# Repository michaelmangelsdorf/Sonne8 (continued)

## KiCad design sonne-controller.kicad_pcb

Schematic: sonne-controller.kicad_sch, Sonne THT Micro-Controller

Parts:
C1, C4, C6, C7, C16, C25, C26: C_Polarized_Small; CP_Radial_D6.3mm_P2.50mm
C2, C3, C5, C8, C9, C10, C11, C12, C13, C14, C15, C17, C19, C20, C21, C22, C23, C24: C_Small; C_Disc_D5.0mm_W2.5mm_P2.50mm
D1, D2: LED; LED_1206_3216Metric_Pad1.42x1.75mm_HandSolder
J1, J2, J4: Conn_01x08_Male; PinHeader_1x08_P2.54mm_Vertical
J3: Conn_01x20_Male; PinHeader_1x20_P2.54mm_Vertical
J5, J6: Conn_01x04_Male; PinHeader_1x04_P2.54mm_Vertical
J7: Conn_02x01; PinHeader_2x01_P2.54mm_Vertical
R1, R2, R3: R7.5k; R_Axial_DIN0207_L6.3mm_D2.5mm_P10.16mm_Horizontal
R4, R5: 500k; R_1206_3216Metric_Pad1.30x1.75mm_HandSolder
RN1, RN2: R_Network08; R_Array_SIP9
U1, U63: 4078; DIP-14_W7.62mm_Socket_LongPads
U2, U3, U5, U6, U7, U8, U19, U20, U25, U26, U29, U32, U49, U87: 74HC193; DIP-16_W7.62mm_Socket_LongPads
U4, U11, U45: 74HC74; DIP-14_W7.62mm_Socket_LongPads
U9, U34, U47, U50, U54, U94: 74AHC08; DIP-14_W7.62mm_Socket_LongPads
U12, U13, U16, U31, U52, U53, U56, U64, U65, U91, U92: 74AHC245; DIP-20_W7.62mm_Socket_LongPads
U14, U15, U21, U22, U23, U24, U69, U77, U78, U80, U81, U83, U89, U90, U96, U97: 74HC157; DIP-16_W7.62mm_Socket_LongPads
U17, U44, U98: 74AHC00; DIP-14_W7.62mm_Socket_LongPads
U18, U55, U60, U67, U68, U79, U82, U95, U99: 74AHC273; DIP-20_W7.62mm_Socket_LongPads
U27, U84: 74AHC02; DIP-14_W7.62mm_Socket_LongPads
U28, U38, U42, U46: 74HC32; DIP-14_W7.62mm_Socket_LongPads
U30, U33, U41, U43, U76, U88: 74AHC04; DIP-14_W7.62mm_Socket_LongPads
U35: KM62256CLP; DIP-28_W15.24mm_Socket_LongPads
U36: SST39SF040; DIP-32_W15.24mm_Socket_LongPads
U39: 4075; DIP-14_W7.62mm_Socket_LongPads
U40: 74HC163; DIP-16_W7.62mm_Socket_LongPads
U51, U72, U85, U86: 74HC238; DIP-16_W7.62mm_Socket_LongPads
U57: 27C080; DIP-32_W15.24mm_Socket_LongPads
U58, U59: 74HC283; DIP-16_W7.62mm_Socket_LongPads
U61: 74HC595; DIP-16_W7.62mm_Socket_LongPads
U62: 74HC165; DIP-16_W7.62mm_Socket_LongPads
U66, U70, U71, U74, U93: 74AHC138; DIP-16_W7.62mm_Socket_LongPads
U73, U75: 74AHC574; DIP-20_W7.62mm_Socket_LongPads
X1: CXO_DIP14; Oscillator_DIP-14

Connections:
+5V: C1.1, C2.1, C3.1, C4.1, C5.1, C6.1, C7.1, C8.1, C9.1, C10.1, C11.1, C12.1, C13.1, C14.1, C15.1, C16.1, C17.1, C19.1, C20.1, C21.1, C22.1, C23.1, C24.1, C25.1, C26.1, J2.5, J5.1, J6.1, J6.2, R1.1, R2.1, R3.1, R4.2, U1.14 (Vdd), U2.11 (~LOAD), U2.16 (VCC), U3.11 (~LOAD), U3.16 (VCC), U4.2 (D), U4.10 (~S), U4.12 (D), U4.13 (~R), U4.14 (VCC), U5.16 (VCC), U6.16 (VCC), U7.16 (VCC), U8.16 (VCC), U9.14 (VCC), U11.2 (D), U11.12 (D), U11.14 (VCC), U12.1 (A->B), U12.20 (VCC), U13.1 (A->B), U13.20 (VCC), U14.16 (VCC), U15.16 (VCC), U16.1 (A->B), U16.20 (VCC), U17.14 (VCC), U18.20 (VCC), U19.4 (DOWN), U19.16 (VCC), U20.4 (DOWN), U20.16 (VCC), U21.16 (VCC), U22.16 (VCC), U23.16 (VCC), U24.16 (VCC), U25.4 (DOWN), U25.16 (VCC), U26.4 (DOWN), U26.16 (VCC), U27.14 (VCC), U28.14 (VCC), U29.4 (DOWN), U29.16 (VCC), U30.14 (VCC), U31.1 (A->B), U31.20 (VCC), U32.16 (VCC), U33.14 (VCC), U34.14 (VCC), U35.28 (VCC), U36.31 (PGM), U36.32 (VCC), U38.14 (VCC), U39.14 (VDD), U40.7 (CEP), U40.9 (~PE), U40.10 (CET), U40.16 (VCC), U41.14 (VCC), U42.14 (VCC), U43.14 (VCC), U44.14 (VCC), U45.2 (D), U45.12 (D), U45.14 (VCC), U46.14 (VCC), U47.14 (VCC), U49.4 (DOWN), U49.16 (VCC), U50.14 (VCC), U51.6 (G1), U51.16 (VCC), U52.1 (A->B), U52.20 (VCC), U53.1 (A->B), U53.9 (A7), U53.20 (VCC), U54.14 (VCC), U55.20 (VCC), U56.1 (A->B), U56.20 (VCC), U57.32 (VCC), U58.16 (VCC), U59.16 (VCC), U60.20 (VCC), U61.16 (VCC), U62.16 (VCC), U63.14 (Vdd), U64.1 (A->B), U64.20 (VCC), U65.1 (A->B), U65.20 (VCC), U66.16 (VCC), U67.20 (VCC), U68.20 (VCC), U69.16 (VCC), U70.16 (VCC), U71.16 (VCC), U72.16 (VCC), U73.20 (VCC), U74.16 (VCC), U75.20 (VCC), U76.14 (VCC), U77.16 (VCC), U78.16 (VCC), U79.20 (VCC), U80.16 (VCC), U81.16 (VCC), U82.20 (VCC), U83.16 (VCC), U84.14 (VCC), U85.16 (VCC), U86.6 (G1), U86.16 (VCC), U87.16 (VCC), U88.14 (VCC), U89.16 (VCC), U90.16 (VCC), U91.1 (A->B), U91.20 (VCC), U92.1 (A->B), U92.20 (VCC), U93.6 (E3), U93.16 (VCC), U94.14 (VCC), U95.20 (VCC), U96.16 (VCC), U97.16 (VCC), U98.14 (VCC), U99.20 (VCC), X1.1 (EN), X1.14 (Vcc); also elsewhere on the board
/A0: U7.3 (QA), U13.2 (A0), U57.27 (A8), U91.2 (A0)
/A1: U7.2 (QB), U13.3 (A1), U57.26 (A9), U91.3 (A1)
/A2: U7.6 (QC), U13.4 (A2), U57.23 (A10), U91.4 (A2)
/A3: U7.7 (QD), U13.5 (A3), U57.25 (A11), U91.5 (A3)
/A4: U8.3 (QA), U13.6 (A4), U57.4 (A12), U91.6 (A4)
/A5: U8.2 (QB), U13.7 (A5), U57.28 (A13), U91.7 (A5)
/A6: U8.6 (QC), U13.8 (A6), U57.29 (A14), U91.8 (A6)
/A7: U8.7 (QD), U13.9 (A7), U57.3 (A15), U91.9 (A7)
/APPLY: U33.4, U66.6 (E3), U70.6 (E3)
/BRANCH: U39.3, U39.9
/CLOSE: J2.4, U9.12, U17.4, U27.6, U40.11 (Q3), U51.4 (~G2A), U84.2, U84.6; also elsewhere on the board
/CSI: U61.11 (SRCLK), U61.12 (RCLK), U76.2
/CSO: U62.2 (CP), U76.4
/DB0: J4.1, RN2.2 (R1), U7.15 (A), U16.18 (B0), U18.3 (D0), U31.18 (B0), U32.15 (A), U35.11 (Q0), U36.13 (D0), U52.18 (B0), U55.3 (D0), U56.18 (B0), U60.3 (D0), U61.15 (QA), U62.11 (D0), U64.18 (B0), U65.18 (B0), U67.3 (D0), U68.3 (D0), U73.2 (D0), U75.19 (Q0), U77.3 (I1a), U80.3 (I1a), U83.3 (I1a), U91.18 (B0), U92.18 (B0), U96.3 (I1a)
/DB1: J4.2, RN2.3 (R2), U7.1 (B), U16.17 (B1), U18.4 (D1), U31.17 (B1), U32.1 (B), U35.12 (Q1), U36.14 (D1), U52.17 (B1), U55.4 (D1), U56.17 (B1), U60.4 (D1), U61.1 (QB), U62.12 (D1), U64.17 (B1), U65.17 (B1), U67.4 (D1), U68.4 (D1), U73.3 (D1), U75.18 (Q1), U77.6 (I1b), U80.6 (I1b), U83.6 (I1b), U91.17 (B1), U92.17 (B1), U96.6 (I1b)
/DB2: J4.3, RN2.4 (R3), U7.10 (C), U16.16 (B2), U18.7 (D2), U31.16 (B2), U32.10 (C), U35.13 (Q2), U36.15 (D2), U52.16 (B2), U55.7 (D2), U56.16 (B2), U60.7 (D2), U61.2 (QC), U62.13 (D2), U64.16 (B2), U65.16 (B2), U67.7 (D2), U68.7 (D2), U73.4 (D2), U75.17 (Q2), U77.10 (I1c), U80.10 (I1c), U83.10 (I1c), U91.16 (B2), U92.16 (B2), U96.10 (I1c)
/DB3: J4.4, RN2.5 (R4), U7.9 (D), U16.15 (B3), U18.8 (D3), U31.15 (B3), U32.9 (D), U35.15 (Q3), U36.17 (D3), U52.15 (B3), U55.8 (D3), U56.15 (B3), U60.8 (D3), U61.3 (QD), U62.14 (D3), U64.15 (B3), U65.15 (B3), U67.8 (D3), U68.8 (D3), U73.5 (D3), U75.16 (Q3), U77.13 (I1d), U80.13 (I1d), U83.13 (I1d), U91.15 (B3), U92.15 (B3), U96.13 (I1d)
/DB4: J4.5, RN2.6 (R5), U8.15 (A), U16.14 (B4), U18.13 (D4), U31.14 (B4), U35.16 (Q4), U36.18 (D4), U52.14 (B4), U55.13 (D4), U56.14 (B4), U60.13 (D4), U61.4 (QE), U62.3 (D4), U64.14 (B4), U65.14 (B4), U67.13 (D4), U68.13 (D4), U69.3 (I1a), U73.6 (D4), U75.15 (Q4), U78.3 (I1a), U81.3 (I1a), U87.15 (A), U91.14 (B4), U92.14 (B4), U97.3 (I1a)
/DB5: J4.6, RN2.7 (R6), U8.1 (B), U16.13 (B5), U18.14 (D5), U31.13 (B5), U35.17 (Q5), U36.19 (D5), U52.13 (B5), U55.14 (D5), U56.13 (B5), U60.14 (D5), U61.5 (QF), U62.4 (D5), U64.13 (B5), U65.13 (B5), U67.14 (D5), U68.14 (D5), U69.6 (I1b), U73.7 (D5), U75.14 (Q5), U78.6 (I1b), U81.6 (I1b), U87.1 (B), U91.13 (B5), U92.13 (B5), U97.6 (I1b)
/DB6: J4.7, RN2.8 (R7), U8.10 (C), U16.12 (B6), U18.17 (D6), U31.12 (B6), U35.18 (Q6), U36.20 (D6), U52.12 (B6), U55.17 (D6), U56.12 (B6), U60.17 (D6), U61.6 (QG), U62.5 (D6), U64.12 (B6), U65.12 (B6), U67.17 (D6), U68.17 (D6), U69.10 (I1c), U73.8 (D6), U75.13 (Q6), U78.10 (I1c), U81.10 (I1c), U87.10 (C), U91.12 (B6), U92.12 (B6), U97.10 (I1c)
/DB7: J4.8, RN2.9 (R8), U8.9 (D), U16.11 (B7), U18.18 (D7), U31.11 (B7), U35.19 (Q7), U36.21 (D7), U52.11 (B7), U55.18 (D7), U56.11 (B7), U60.18 (D7), U61.7 (QH), U62.6 (D7), U64.11 (B7), U65.11 (B7), U67.18 (D7), U68.18 (D7), U69.13 (I1d), U73.9 (D7), U75.12 (Q7), U78.13 (I1d), U81.13 (I1d), U87.9 (D), U91.11 (B7), U92.11 (B7), U97.13 (I1d)
/DPH: U17.1, U17.9, U17.12, U27.5, U40.12 (Q2), U51.3 (A2), U71.6 (E3), U88.5, U98.10, U98.12
/E0: U58.4 (S1), U63.2, U99.3 (D0)
/E1: U58.1 (S2), U63.3, U99.4 (D1)
/E2: U58.13 (S3), U63.4, U99.7 (D2)
/E3: U58.10 (S4), U63.5, U99.8 (D3)
/E4: U59.4 (S1), U63.9, U99.13 (D4)
/E5: U59.1 (S2), U63.10, U99.14 (D5)
/E6: U59.13 (S3), U63.11, U99.17 (D6)
/E7: U59.10 (S4), U63.12, U99.18 (D7)
/EXIT: U18.11 (Cp), U30.11, U34.3
/FD0: U14.2 (I0a), U56.2 (A0), U82.2 (Q0)
/FD1: U14.5 (I0b), U56.3 (A1), U82.5 (Q1)
/FD2: U14.11 (I0c), U56.4 (A2), U82.6 (Q2)
/FD3: U14.14 (I0d), U56.5 (A3), U82.9 (Q3)
/FD4: U15.2 (I0a), U56.6 (A4), U82.12 (Q4)
/FD5: U15.5 (I0b), U56.7 (A5), U82.15 (Q5)
/FD6: U15.11 (I0c), U56.8 (A6), U82.16 (Q6)
/FD7: U15.14 (I0d), U56.9 (A7), U82.19 (Q7)
/FETCH: U21.1 (S), U22.1 (S), U23.1 (S), U24.1 (S), U28.6, U42.1
/FIA0: U23.3 (I1a), U25.3 (QA), U80.2 (I0a)
/FIA1: U23.6 (I1b), U25.2 (QB), U80.5 (I0b)
/FIA2: U23.10 (I1c), U25.6 (QC), U80.11 (I0c)
/FIA3: U23.13 (I1d), U25.7 (QD), U80.14 (I0d)
/FIA4: U24.3 (I1a), U26.3 (QA), U81.2 (I0a)
/FIA5: U24.6 (I1b), U26.2 (QB), U81.5 (I0b)
/FIA6: U24.10 (I1c), U26.6 (QC), U81.11 (I0c)
/FIA7: U24.13 (I1d), U26.7 (QD), U81.14 (I0d)
/FOP0: U55.2 (Q0), U57.2 (A16)
/FOP1: U55.5 (Q1), U57.30 (A17)
/FOP2: U55.6 (Q2), U57.31 (A18)
/FOP3: U55.9 (Q3), U57.1 (A19)
/FR0: U2.3 (QA), U14.3 (I1a)
/FR1: U2.2 (QB), U14.6 (I1b)
/FR2: U2.6 (QC), U14.10 (I1c)
/FR3: U2.7 (QD), U14.13 (I1d)
/FR4: U3.3 (QA), U15.3 (I1a)
/FR5: U3.2 (QB), U15.6 (I1b)
/FR6: U3.6 (QC), U15.10 (I1c)
/FR7: U3.7 (QD), U15.13 (I1d)
/G0: U5.3 (QA), U12.2 (A0), U16.2 (A0), U95.3 (D0)
/G1: U5.2 (QB), U12.3 (A1), U16.3 (A1), U95.4 (D1)
/G2: U5.6 (QC), U12.4 (A2), U16.4 (A2), U95.7 (D2)
/G3: U5.7 (QD), U12.5 (A3), U16.5 (A3), U95.8 (D3)
/G4: U6.3 (QA), U12.6 (A4), U16.6 (A4), U95.13 (D4)
/G5: U6.2 (QB), U12.7 (A5), U16.7 (A5), U95.14 (D5)
/G6: U6.6 (QC), U12.8 (A6), U16.8 (A6), U95.17 (D6)
/G7: U6.7 (QD), U12.9 (A7), U16.9 (A7), U95.18 (D7)
/Gx_pre: U47.9, U86.13 (Y2), U88.13
/IB0: U53.2 (A0), U60.2 (Q0), U65.2 (A0), U66.1 (A0), U70.1 (A0), U72.1 (A0), U74.1 (A0), U85.1 (A0)
/IB1: U53.3 (A1), U60.5 (Q1), U65.3 (A1), U66.2 (A1), U70.2 (A1), U72.2 (A1), U74.2 (A1), U85.2 (A1)
/IB2: U53.4 (A2), U60.6 (Q2), U65.4 (A2), U66.3 (A2), U70.3 (A2), U72.3 (A2), U74.3 (A2), U85.3 (A2)
/IB3: U60.9 (Q3), U65.5 (A3), U66.4 (E1), U70.4 (E1), U72.6 (G1), U74.6 (E3), U84.9, U85.5 (~G2B), U93.1 (A0)
/IB4: U53.8 (A6), U60.12 (Q4), U65.6 (A4), U71.1 (A0), U86.1 (A0)
/IB5: U60.15 (Q5), U65.7 (A5), U71.2 (A1), U86.2 (A1), U93.2 (A1)
/IB6: U60.16 (Q6), U71.3 (A2), U86.3 (A2), U88.11, U98.4
/IB7: U39.11, U60.19 (Q7), U71.4 (E1), U86.4 (~G2A), U98.1, U98.9
/IN_BASE: U23.15 (E), U24.15 (E), U34.11
/IN_LOCAL: U14.1 (S), U15.1 (S), U22.12 (Zd), U28.1, U34.12, U35.1 (A14)
/IO0: J1.8, RN1.9 (R8), U73.19 (Q0), U75.2 (D0)
/IO1: J1.7, RN1.8 (R7), U73.18 (Q1), U75.3 (D1)
/IO2: J1.6, RN1.7 (R6), U73.17 (Q2), U75.4 (D2)
/IO3: J1.5, RN1.6 (R5), U73.16 (Q3), U75.5 (D3)
/IO4: J1.4, RN1.5 (R4), U73.15 (Q4), U75.6 (D4)
/IO5: J1.3, RN1.4 (R3), U73.14 (Q5), U75.7 (D5)
/IO6: J1.2, RN1.3 (R2), U73.13 (Q6), U75.8 (D6)
/IO7: J1.1, RN1.2 (R1), U73.12 (Q7), U75.9 (D7)
/IPH: U27.4, U28.4
/LFETCH: U54.3, U84.3
/Lx: U28.5, U33.6
/Lx_pre: U47.1, U54.5, U86.14 (Y1)
/MISO: J2.6, R2.2, U41.11; also elsewhere on the board
/MOSI: J2.7, U62.9 (Q7); also elsewhere on the board
/Mx: U27.8, U33.10
/Mx_pre: U47.5, U86.11 (Y4)
/NZFLAG_F: U34.4, U63.1
/OFFS0: U55.12 (Q4), U58.5 (A1)
/OFFS1: U55.15 (Q5), U58.3 (A2)
/OFFS2: U55.16 (Q6), U58.14 (A3)
/OFFS3: U55.19 (Q7), U58.12 (A4), U59.3 (A2), U59.5 (A1), U59.12 (A4), U59.14 (A3)
/PH0: R5.2, U43.3, U51.15 (Y0), U86.5 (~G2B)
/PH1: U44.4, U51.13 (Y2), U54.2, U60.11 (Cp), U99.11 (Cp)
/PH2: U51.11 (Y4)
/PH3: U34.2, U43.11, U51.9 (Y6)
/PIA0: U19.3 (QA), U21.3 (I1a), U83.2 (I0a)
/PIA1: U19.2 (QB), U21.6 (I1b), U83.5 (I0b)
/PIA2: U19.6 (QC), U21.10 (I1c), U83.11 (I0c)
/PIA3: U19.7 (QD), U21.13 (I1d), U83.14 (I0d)
/PIA4: U20.3 (QA), U22.3 (I1a), U69.2 (I0a)
/PIA5: U20.2 (QB), U22.6 (I1b), U69.5 (I0b)
/PIA6: U20.6 (QC), U22.10 (I1c), U69.11 (I0c)
/PIA7: U20.7 (QD), U22.13 (I1d), U69.14 (I0d)
/Px: U33.12, U75.11 (Cp)
/Q0: U32.3 (QA), U57.12 (A0), U92.2 (A0)
/Q1: U32.2 (QB), U57.11 (A1), U92.3 (A1)
/Q2: U32.6 (QC), U57.10 (A2), U92.4 (A2)
/Q3: U32.7 (QD), U57.9 (A3), U92.5 (A3)
/Q4: U57.8 (A4), U87.3 (QA), U92.6 (A4)
/Q5: U57.7 (A5), U87.2 (QB), U92.7 (A5)
/Q6: U57.6 (A6), U87.6 (QC), U92.8 (A6)
/Q7: U57.5 (A7), U87.7 (QD), U92.9 (A7)
/RES: U2.14 (CLR), U3.14 (CLR), U5.14 (CLR), U6.14 (CLR), U7.14 (CLR), U8.14 (CLR), U25.14 (CLR), U26.14 (CLR), U27.12, U29.14 (CLR), U32.14 (CLR), U38.2, U41.1, U41.6, U49.14 (CLR), U84.5, U87.14 (CLR)
/RET: U28.13, U33.8
/Rx_pre: U47.12, U86.12 (Y3)
/SCL: U27.11, U76.6
/SCLK: J2.8, U45.5 (Q); also elsewhere on the board
/SCROUNGE: U1.1, U39.13, U71.5 (E2)
/SIG: U66.5 (E2), U72.4 (~G2A), U76.8
/SIG_pre: U85.4 (~G2A), U86.15 (Y0)
/TRAP: U30.12, U38.4, U39.4
/UH0: J3.1, U68.2 (Q0); also elsewhere on the board
/UH1: J3.2, U68.5 (Q1); also elsewhere on the board
/UH2: J3.3, U68.6 (Q2); also elsewhere on the board
/UH3: J3.4, U68.9 (Q3); also elsewhere on the board
/UL0: J3.5, U68.12 (Q4); also elsewhere on the board
/UL1: J3.6, U68.15 (Q5); also elsewhere on the board
/UL2: J3.7, U68.16 (Q6); also elsewhere on the board
/UL3: J3.8, U68.19 (Q7); also elsewhere on the board
/VH0: J3.9, U67.2 (Q0); also elsewhere on the board
/VH1: J3.10, U67.5 (Q1); also elsewhere on the board
/VH2: J3.11, U67.6 (Q2); also elsewhere on the board
/VH3: J3.12, U67.9 (Q3); also elsewhere on the board
/VL0: J3.13, U67.12 (Q4); also elsewhere on the board
/VL1: J3.14, U67.15 (Q5); also elsewhere on the board
/VL2: J3.15, U67.16 (Q6); also elsewhere on the board
/VL3: J3.16, U67.19 (Q7); also elsewhere on the board
/XA0: U53.18 (B0), U89.2 (I0a)
/XA1: U53.17 (B1), U89.5 (I0b)
/XA2: U53.16 (B2), U89.11 (I0c)
/XA3: U53.15 (B3), U89.14 (I0d)
/XA4: U53.14 (B4), U90.2 (I0a)
/XA5: U53.13 (B5), U90.5 (I0b)
/XA6: U53.12 (B6), U90.11 (I0c)
/XA7: U53.11 (B7), U90.14 (I0d)
/Y0: U31.2 (A0), U77.2 (I0a), U79.2 (Q0)
/Y1: U31.3 (A1), U77.5 (I0b), U79.5 (Q1)
/Y2: U31.4 (A2), U77.11 (I0c), U79.6 (Q2)
/Y3: U31.5 (A3), U77.14 (I0d), U79.9 (Q3)
/Y4: U31.6 (A4), U78.2 (I0a), U79.12 (Q4)
/Y5: U31.7 (A5), U78.5 (I0b), U79.15 (Q5)
/Y6: U31.8 (A6), U78.11 (I0c), U79.16 (Q6)
/Y7: U31.9 (A7), U78.14 (I0d), U79.19 (Q7)
/ZFLAG_F: U34.9, U63.13
/xB: U39.1, U72.15 (Y0)
/xC: U30.9, U39.5, U46.4, U72.12 (Y3)
/xE: U34.10, U72.13 (Y2)
/xG_pre: U47.10, U85.13 (Y2), U94.2
/xM_pre: U47.2, U47.4, U85.11 (Y4)
/xP: U30.4, U73.11 (Cp)
/xR_pre: U47.13, U85.12 (Y3)
/xT: U34.5, U72.14 (Y1)
/xU: U68.11 (Cp), U72.9 (Y6)
/xV: U67.11 (Cp), U72.7 (Y7)
/xX: U69.1 (S), U72.11 (Y4), U76.11, U83.1 (S)
/xY: U46.5, U72.10 (Y5), U80.1 (S), U81.1 (S)
/~APPLY: U33.3, U39.10, U72.5 (~G2B), U74.5 (E2)
/~BOA: U7.13 (~BO), U8.4 (DOWN)
/~BOF: U2.13 (~BO), U3.4 (DOWN)
/~BOG: U5.13 (~BO), U6.4 (DOWN)
/~BOQ: U32.13 (~BO), U87.4 (DOWN)
/~CLEAR: U4.4 (~S), U27.1
/~CLIP: U17.11, U94.10, U96.1 (S), U97.1 (S)
/~COA: U7.12 (~CO), U8.5 (UP)
/~COF: U2.12 (~CO), U3.5 (UP)
/~COG: U5.12 (~CO), U6.5 (UP)
/~COQ: U32.12 (~CO), U87.5 (UP)
/~CSI: U70.14 (O1), U76.1
/~CSO: U70.13 (O2), U76.3
/~DEA: U7.4 (DOWN), U74.12 (O3)
/~DEG: U5.4 (DOWN), U74.10 (O5)
/~DEQ: U32.4 (DOWN), U74.14 (O1)
/~DPH: U28.10, U88.6
/~ENTER: U2.4 (DOWN), U74.7 (O7)
/~EXIT: U11.4 (~S), U30.10
/~Fx: U64.19 (CE), U71.10 (O5)
/~GETA: U42.12, U93.15 (O0)
/~GETQ: U38.13, U93.13 (O2)
/~Gx: U16.19 (CE), U71.13 (O2)
/~HOLD: U41.4, U46.9
/~INA: U7.5 (UP), U74.13 (O2)
/~ING: U5.5 (UP), U74.11 (O4)
/~INQ: U32.5 (UP), U74.15 (O0)
/~IN_RAM: U30.2, U35.20 (~CS)
/~IN_ROM: U28.3, U30.1, U36.22 (CE)
/~LEAVE: U2.5 (UP), U74.9 (O6)
/~LID: U17.3, U25.5 (UP), U43.9
/~Lx: U33.5, U71.14 (O1)
/~MEMOE: U27.10, U35.22 (~OE), U36.24 (OE)
/~Mx: U33.11, U71.11 (O4)
/~OFF: U9.9, U70.10 (O5)
/~PH0: U4.1 (~R), U11.1 (~R), U43.4, U46.10, U60.1 (~Mr), U85.6 (G1)
/~PH3: U38.12, U39.12, U42.5, U42.9, U42.13, U43.10, U46.12
/~POE: U45.9 (Q), U73.1 (OE)
/~PULL: U17.8, U46.13, U52.19 (CE), U77.1 (S), U78.1 (S), U94.5
/~PUTA: U42.4, U91.19 (CE), U93.14 (O1)
/~PUTQ: U42.10, U92.19 (CE), U93.12 (O3)
/~Px: U33.13, U71.7 (O7), U75.1 (OE)
/~RES: J5.3, U9.10, U18.1 (~Mr), U41.2, U50.12, U55.1 (~Mr), U61.10 (~SRCLR), U67.1 (~Mr), U68.1 (~Mr), U79.1 (~Mr), U82.1 (~Mr), U95.1 (~Mr), U99.1 (~Mr)
/~RET: U19.11 (~LOAD), U20.11 (~LOAD), U31.19 (CE), U33.9, U98.11
/~Rx: U56.19 (CE), U71.12 (O3)
/~SCH: U45.4 (~S), U70.11 (O4)
/~SCL: U70.12 (O3), U76.5
/~SETA: U70.9 (O6), U94.4
/~SETG: U50.13, U70.7 (O7)
/~SIG: U70.5 (E2), U71.15 (O0), U74.4 (E1), U76.9
/~Sx: U61.13 (~OE), U71.9 (O6)
/~TRAP: U28.8, U30.13, U50.9, U65.19 (CE)
/~XFER: U84.8, U89.1 (S), U90.1 (S), U93.5 (E2), U98.6
/~XINC: U29.5 (UP), U44.6
/~atA: U11.10 (~S), U94.6
/~atG: U11.13 (~R), U50.11
/~xA: U9.1, U66.14 (O1)
/~xC: U30.8, U50.1
/~xF: U43.5, U66.10 (O5)
/~xG: U66.13 (O2), U94.9
/~xM: U54.13, U66.11 (O4)
/~xP: U30.3, U45.13 (~R), U66.7 (O7)
/~xQ: U50.4, U66.15 (O0)
/~xR: U44.13, U66.12 (O3)
/~xS: U62.1 (~PL), U66.9 (O6)
/~xX: U50.2, U76.10
GND: C1.2, C2.2, C3.2, C4.2, C5.2, C6.2, C7.2, C8.2, C9.2, C10.2, C11.2, C12.2, C13.2, C14.2, C15.2, C16.2, C17.2, C19.2, C20.2, C21.2, C22.2, C23.2, C24.2, C25.2, C26.2, D1.1 (K), D2.1 (K), J2.1, J5.2, J6.3, J6.4, RN1.1 (common), RN2.1 (common), U1.7 (Vss), U1.9, U1.10, U1.11, U1.12, U2.1 (B), U2.8 (GND), U2.9 (D), U2.10 (C), U2.15 (A), U3.1 (B), U3.8 (GND), U3.9 (D), U3.10 (C), U3.15 (A), U4.3 (C), U4.7 (GND), U4.11 (C), U5.8 (GND), U6.8 (GND), U7.8 (GND), U8.8 (GND), U9.7 (GND), U11.3 (C), U11.7 (GND), U11.11 (C), U12.10 (GND), U13.10 (GND), U14.8 (GND), U14.15 (E), U15.8 (GND), U15.15 (E), U16.10 (GND), U17.7 (GND), U18.10 (GND), U19.8 (GND), U20.8 (GND), U21.8 (GND), U21.15 (E), U22.8 (GND), U22.15 (E), U23.8 (GND), U24.8 (GND), U25.8 (GND), U26.8 (GND), U27.7 (GND), U28.7 (GND), U29.8 (GND), U30.5, U30.7 (GND), U31.10 (GND), U32.8 (GND), U33.7 (GND), U34.7 (GND), U35.14 (GND), U36.1 (A18), U36.2 (A16), U36.3 (A15), U36.16 (GND), U36.29 (A14), U36.30 (A17), U38.7 (GND), U38.9, U38.10, U39.7 (VSS), U40.3 (D0), U40.4 (D1), U40.5 (D2), U40.6 (D3), U40.8 (GND), U41.7 (GND), U42.7 (GND), U43.7 (GND), U43.13, U44.1, U44.2, U44.7 (GND), U44.9, U44.10, U45.3 (C), U45.7 (GND), U45.11 (C), U46.1, U46.2, U46.7 (GND), U47.7 (GND), U49.8 (GND), U50.7 (GND), U51.5 (~G2B), U51.8 (GND), U52.10 (GND), U53.5 (A3), U53.6 (A4), U53.7 (A5), U53.10 (GND), U53.19 (CE), U54.7 (GND), U55.10 (GND), U56.10 (GND), U57.16 (GND), U57.22 (~CE), U57.24 (~OE), U58.7 (C0), U58.8 (GND), U59.8 (GND), U60.10 (GND), U61.8 (GND), U62.8 (GND), U62.10 (DS), U62.15 (~CE), U63.7 (Vss), U64.10 (GND), U65.8 (A6), U65.9 (A7), U65.10 (GND), U66.8 (GND), U67.10 (GND), U68.10 (GND), U69.8 (GND), U69.15 (E), U70.8 (GND), U71.8 (GND), U72.8 (GND), U73.10 (GND), U74.8 (GND), U75.10 (GND), U76.7 (GND), U77.8 (GND), U77.15 (E), U78.8 (GND), U78.15 (E), U79.10 (GND), U80.8 (GND), U80.15 (E), U81.8 (GND), U81.15 (E), U82.10 (GND), U83.8 (GND), U83.15 (E), U84.7 (GND), U84.11, U84.12, U85.8 (GND), U86.8 (GND), U87.8 (GND), U88.1, U88.3, U88.7 (GND), U88.9, U89.8 (GND), U89.15 (E), U90.8 (GND), U90.15 (E), U91.10 (GND), U92.10 (GND), U93.3 (A2), U93.4 (E1), U93.8 (GND), U94.7 (GND), U95.10 (GND), U96.8 (GND), U96.15 (E), U97.8 (GND), U97.15 (E), U98.7 (GND), U99.10 (GND), X1.7 (GND); also elsewhere on the board
unnamed: D1.2 (A), R4.1
unnamed: D2.2 (A), R5.1
unnamed 245: J2.2, R1.2, U41.5; also elsewhere on the board
unnamed 246: J2.3, R3.2, U41.9; also elsewhere on the board
unnamed: J5.4, J7.1
unnamed: J7.2, U9.5, X1.8 (OUT)
unnamed: U1.2, U47.3, U76.13, U98.13
unnamed: U1.3, U17.2, U44.5, U47.11
unnamed: U1.4, U17.13, U47.8
unnamed: U1.5, U17.10, U47.6
unnamed: U4.5 (Q), U9.13
unnamed: U5.1 (B), U96.7 (Zb)
unnamed: U5.9 (D), U96.12 (Zd)
unnamed: U5.10 (C), U96.9 (Zc)
unnamed: U5.11 (~LOAD), U6.11 (~LOAD), U94.8
unnamed: U5.15 (A), U96.4 (Za)
unnamed: U6.1 (B), U97.7 (Zb)
unnamed: U6.9 (D), U97.12 (Zd)
unnamed: U6.10 (C), U97.9 (Zc)
unnamed: U6.15 (A), U97.4 (Za)
unnamed: U7.11 (~LOAD), U8.11 (~LOAD), U94.11
unnamed: U9.3, U94.13
unnamed: U11.5 (Q), U17.5
unnamed: U11.8 (~Q), U13.19 (CE)
unnamed: U11.9 (Q), U12.19 (CE)
unnamed: U12.11 (B7), U13.11 (B7), U90.13 (I1d)
unnamed: U12.12 (B6), U13.12 (B6), U90.10 (I1c)
unnamed: U12.13 (B5), U13.13 (B5), U90.6 (I1b)
unnamed: U12.14 (B4), U13.14 (B4), U90.3 (I1a)
unnamed: U12.15 (B3), U13.15 (B3), U89.13 (I1d)
unnamed: U12.16 (B2), U13.16 (B2), U89.10 (I1c)
unnamed: U12.17 (B1), U13.17 (B1), U89.6 (I1b)
unnamed: U12.18 (B0), U13.18 (B0), U89.3 (I1a)
unnamed: U14.4 (Za), U23.2 (I0a)
unnamed: U14.7 (Zb), U23.5 (I0b)
unnamed: U14.9 (Zc), U23.11 (I0c)
unnamed: U14.12 (Zd), U23.14 (I0d)
unnamed: U15.4 (Za), U24.2 (I0a)
unnamed: U15.7 (Zb), U24.5 (I0b)
unnamed: U15.9 (Zc), U24.11 (I0c)
unnamed: U15.12 (Zd), U24.14 (I0d)
unnamed: U17.6, U25.11 (~LOAD), U26.11 (~LOAD)
unnamed: U18.2 (Q0), U25.15 (A)
unnamed: U18.5 (Q1), U25.1 (B)
unnamed: U18.6 (Q2), U25.10 (C)
unnamed: U18.9 (Q3), U25.9 (D)
unnamed: U18.12 (Q4), U26.15 (A)
unnamed: U18.15 (Q5), U26.1 (B)
unnamed: U18.16 (Q6), U26.10 (C)
unnamed: U18.19 (Q7), U26.9 (D)
unnamed: U19.1 (B), U29.2 (QB), U52.3 (A1)
unnamed: U19.5 (UP), U84.1
unnamed: U19.9 (D), U29.7 (QD), U52.5 (A3)
unnamed: U19.10 (C), U29.6 (QC), U52.4 (A2)
unnamed: U19.12 (~CO), U20.5 (UP)
unnamed: U19.14 (CLR), U20.14 (CLR), U38.3
unnamed: U19.15 (A), U29.3 (QA), U52.2 (A0)
unnamed: U20.1 (B), U49.2 (QB), U52.7 (A5)
unnamed: U20.9 (D), U49.7 (QD), U52.9 (A7)
unnamed: U20.10 (C), U49.6 (QC), U52.8 (A6)
unnamed: U20.15 (A), U49.3 (QA), U52.6 (A4)
unnamed: U21.2 (I0a), U89.4 (Za)
unnamed: U21.4 (Za), U35.10 (A0), U36.12 (A0)
unnamed: U21.5 (I0b), U89.7 (Zb)
unnamed: U21.7 (Zb), U35.9 (A1), U36.11 (A1)
unnamed: U21.9 (Zc), U35.8 (A2), U36.10 (A2)
unnamed: U21.11 (I0c), U89.9 (Zc)
unnamed: U21.12 (Zd), U35.7 (A3), U36.9 (A3)
unnamed: U21.14 (I0d), U89.12 (Zd)
unnamed: U22.2 (I0a), U90.4 (Za)
unnamed: U22.4 (Za), U35.6 (A4), U36.8 (A4)
unnamed: U22.5 (I0b), U90.7 (Zb)
unnamed: U22.7 (Zb), U35.5 (A5), U36.7 (A5)
unnamed: U22.9 (Zc), U33.1, U35.4 (A6), U36.6 (A6)
unnamed: U22.11 (I0c), U90.9 (Zc)
unnamed: U22.14 (I0d), U90.12 (Zd)
unnamed: U23.4 (Za), U35.3 (A7), U36.5 (A7)
unnamed: U23.7 (Zb), U35.25 (A8), U36.27 (A8)
unnamed: U23.9 (Zc), U35.24 (A9), U36.26 (A9)
unnamed: U23.12 (Zd), U35.21 (A10), U36.23 (A10)
unnamed: U24.4 (Za), U35.23 (A11), U36.25 (A11)
unnamed: U24.7 (Zb), U35.2 (A12), U36.4 (A12)
unnamed: U24.9 (Zc), U35.26 (A13), U36.28 (A13)
unnamed: U24.12 (Zd), U28.2
unnamed: U25.12 (~CO), U26.5 (UP)
unnamed: U27.2, U43.8
unnamed: U27.3, U28.12, U39.6
unnamed: U27.9, U42.3
unnamed: U27.13, U45.1 (~R)
unnamed: U28.9, U98.3
unnamed: U28.11, U34.1
unnamed: U29.1 (B), U83.7 (Zb)
unnamed: U29.9 (D), U83.12 (Zd)
unnamed: U29.10 (C), U83.9 (Zc)
unnamed: U29.11 (~LOAD), U49.11 (~LOAD), U50.8
unnamed: U29.12 (~CO), U49.5 (UP)
unnamed: U29.15 (A), U83.4 (Za)
unnamed: U32.11 (~LOAD), U50.6, U87.11 (~LOAD)
unnamed: U33.2, U34.13
unnamed: U34.6, U39.2
unnamed: U34.8, U39.8
unnamed: U35.27 (~WE), U54.11
unnamed: U9.11, U38.1
unnamed: U38.5, U46.6
unnamed: U38.6, U79.11 (Cp)
unnamed: U38.11, U50.5
unnamed: U40.1 (~MR), U84.4
unnamed: U9.6, U40.2 (CP)
unnamed: U40.13 (Q1), U51.2 (A1)
unnamed: U40.14 (Q0), U51.1 (A0)
unnamed: U41.3, U41.8
unnamed: U41.10, U41.13
unnamed: U41.12, U61.14 (SER)
unnamed: U42.2, U84.10
unnamed: U42.6, U54.9
unnamed: U42.8, U54.10
unnamed: U42.11, U94.12
unnamed: U43.1, U98.8
unnamed: U43.2, U98.5
unnamed: U43.6, U55.11 (Cp)
unnamed: U44.11, U82.11 (Cp)
unnamed: U9.2, U44.12, U46.11
unnamed: U9.8, U45.10 (~S)
unnamed: U9.4, U46.8
unnamed: U49.1 (B), U69.7 (Zb)
unnamed: U49.9 (D), U69.12 (Zd)
unnamed: U49.10 (C), U69.9 (Zc)
unnamed: U49.15 (A), U69.4 (Za)
unnamed: U50.3, U50.10
unnamed: U54.1, U54.6
unnamed: U54.4, U76.12
unnamed: U54.8, U54.12
unnamed: U57.13 (D0), U58.6 (B1)
unnamed: U57.14 (D1), U58.2 (B2)
unnamed: U57.15 (D2), U58.15 (B3)
unnamed: U57.17 (D3), U58.11 (B4)
unnamed: U57.18 (D4), U59.6 (B1)
unnamed: U57.19 (D5), U59.2 (B2)
unnamed: U57.20 (D6), U59.15 (B3)
unnamed: U57.21 (D7), U59.11 (B4)
unnamed: U58.9 (C4), U59.7 (C0)
unnamed: U64.2 (A0), U99.2 (Q0)
unnamed: U64.3 (A1), U99.5 (Q1)
unnamed: U64.4 (A2), U99.6 (Q2)
unnamed: U64.5 (A3), U99.9 (Q3)
unnamed: U64.6 (A4), U99.12 (Q4)
unnamed: U64.7 (A5), U99.15 (Q5)
unnamed: U64.8 (A6), U99.16 (Q6)
unnamed: U64.9 (A7), U99.19 (Q7)
unnamed: U77.4 (Za), U82.3 (D0)
unnamed: U77.7 (Zb), U82.4 (D1)
unnamed: U77.9 (Zc), U82.7 (D2)
unnamed: U77.12 (Zd), U82.8 (D3)
unnamed: U78.4 (Za), U82.13 (D4)
unnamed: U78.7 (Zb), U82.14 (D5)
unnamed: U78.9 (Zc), U82.17 (D6)
unnamed: U78.12 (Zd), U82.18 (D7)
unnamed: U79.3 (D0), U80.4 (Za)
unnamed: U79.4 (D1), U80.7 (Zb)
unnamed: U79.7 (D2), U80.9 (Zc)
unnamed: U79.8 (D3), U80.12 (Zd)
unnamed: U79.13 (D4), U81.4 (Za)
unnamed: U79.14 (D5), U81.7 (Zb)
unnamed: U79.17 (D6), U81.9 (Zc)
unnamed: U79.18 (D7), U81.12 (Zd)
unnamed: U88.10, U98.2
unnamed: U88.12, U94.1
unnamed: U94.3, U95.11 (Cp)
unnamed: U95.2 (Q0), U96.2 (I0a)
unnamed: U95.5 (Q1), U96.5 (I0b)
unnamed: U95.6 (Q2), U96.11 (I0c)
unnamed: U95.9 (Q3), U96.14 (I0d)
unnamed: U95.12 (Q4), U97.2 (I0a)
unnamed: U95.15 (Q5), U97.5 (I0b)
unnamed: U95.16 (Q6), U97.11 (I0c)
unnamed: U95.19 (Q7), U97.14 (I0d)

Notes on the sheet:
Instruction Latch
Default Pointer
FIP0-7 bus Frame/Instruction/Pending Required for PULL (Branch to return to)
Dual-source low order bit 7 Record segments have 64 bytes only and when IN_LOCAL, high order bit 7 of FL overridden, lost otherwise
PIP0-7 bus Pointer/Instruction/Pending (Pointer to return to in pending code branch)
ALU opcode
PIA0-7 bus Pointer/Instruction/Active
Implements SPI functionality with dedicated SER/DES registers
PDA0-7 bus Pointer/Data/ALU
Effective Frame number (Record or Row or Branch)
Master/ Sources
~4MHz
Toggle G/A
ROM: 16k ROWS/ BRANCHES
Clear Program Counter Applied during CLOSE
Hard-coded select GLOBAL 80h LOCAL C0h
(Active code branch)
Low Order Address = Pointers
Implement an 8-bit parallel tri-state interface bus with dedicated In/Out ports
Targets
CODE or DATA
DATA ACCESS FRAME-NUMBERS
(Pending code branch)
Serial IO
Register ~{CLEAR} signal, apply during CLOSE Reset register in PH0
DATA ACCESS POINTERS
Memory
High Order Address = Frame Numbers
Spare Units
VLSI Footprint
Scrounger prevents XFER pairs NM and MM, reassigning to LID and RET
FD0-7 bus Frame/Data (Active row)
0 IDQ ("Identity Q" / OP:=Q) 1 IDA ("Identity A" / OP:=A) 2 OCQ ("Ones Complement Q" / OP:=~Q) 3 OCA ("Ones Complement A" / OP:=~A) 4 SLQ ("Shift left Q" / OP:=Q<<1) 5 SLA ("Shift left A" / OP:=A<<1) 6 SRQ ("Shift right arithmetic Q" / OP:=Q>>1) 7 SRA ("Shift right arithmetic A" / OP:=A>>1)
Storage
A/Q
Transfers
~{HOLD} request
Preselect
APPLY Decoder
Branch if F result zero

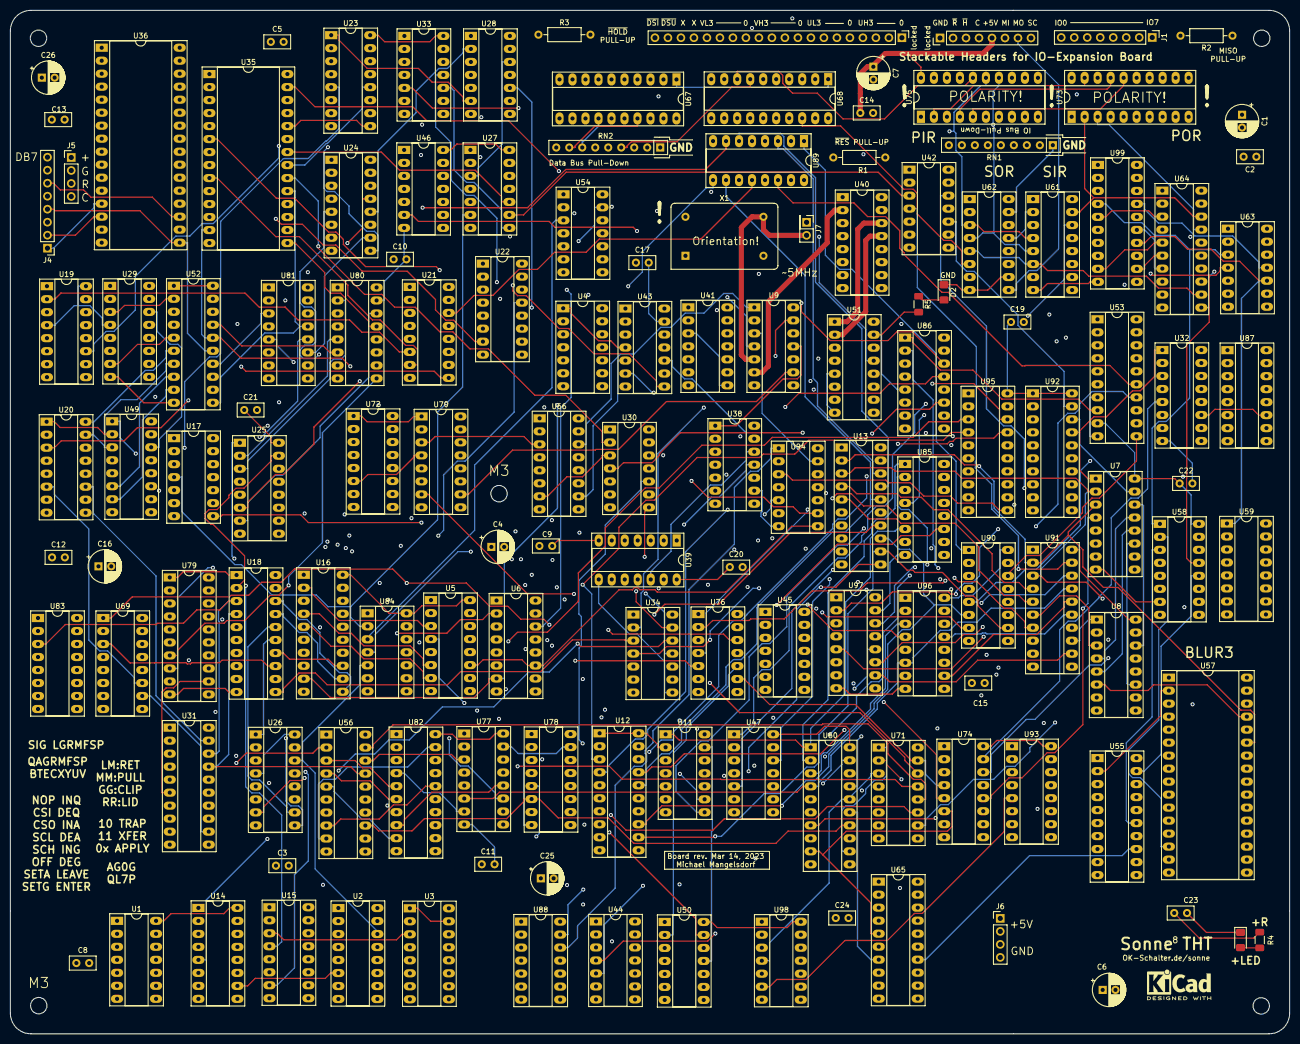
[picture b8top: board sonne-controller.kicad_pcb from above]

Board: 4 copper layers, 250.0 x 200.0 mm, 138 parts (0 on the bottom side), 418 nets.

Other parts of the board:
locked: Conn_01x08_Male; PinHeader_1x08_P2.54mm_Vertical
locked#2: Conn_01x20_Male; PinHeader_1x20_P2.54mm_Vertical

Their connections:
+5V: locked.5; also elsewhere on the board
/CLOSE: locked.4; also elsewhere on the board
/MISO: locked.6; also elsewhere on the board
/MOSI: locked.7; also elsewhere on the board
/SCLK: locked.8; also elsewhere on the board
/UH0: locked#2.1; also elsewhere on the board
/UH1: locked#2.2; also elsewhere on the board
/UH2: locked#2.3; also elsewhere on the board
/UH3: locked#2.4; also elsewhere on the board
/UL0: locked#2.5; also elsewhere on the board
/UL1: locked#2.6; also elsewhere on the board
/UL2: locked#2.7; also elsewhere on the board
/UL3: locked#2.8; also elsewhere on the board
/VH0: locked#2.9; also elsewhere on the board
/VH1: locked#2.10; also elsewhere on the board
/VH2: locked#2.11; also elsewhere on the board
/VH3: locked#2.12; also elsewhere on the board
/VL0: locked#2.13; also elsewhere on the board
/VL1: locked#2.14; also elsewhere on the board
/VL2: locked#2.15; also elsewhere on the board
/VL3: locked#2.16; also elsewhere on the board
GND: locked.1; also elsewhere on the board
unnamed 245: locked.2; also elsewhere on the board
unnamed 246: locked.3; also elsewhere on the board

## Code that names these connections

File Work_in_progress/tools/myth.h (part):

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#define xS 6  /*to SERIAL output*/
#define xP 7  /*to PARALLEL output*/
#define xE 8  /*to ENABLE register*/
#define xJ 9  /*to JUMP page index*/
#define xW 10 /*to WHILE page index*/
#define xT 11 /*to TRUE page index*/
#define xF 12 /*to FALSE page index*/
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#define xA 14 /*to A accumulator*/
#define xB 15 /*to B accumulator*/

#define IDA 0 /*Identity A*/
#define IDB 1 /*Identity B*/
#define OCA 2 /*Ones' complement of A*/
#define OCB 3 /*Ones' complement of B*/
#define SLA 4 /*Shift left A*/
#define SLB 5 /*Shift left B*/
#define SRA 6 /*Shift right A*/
#define SRB 7 /*Shift right B*/
#define AND 8 /*A AND B*/
#define IOR 9 /*A OR B*/
#define EOR 10 /*A XOR B*/
#define ADD 11 /*A + B*/
#define CAR 12 /*Carry of A + B (0 or 1)*/
#define ALB 13 /*255 if A<B else 0*/
#define AEB 14 /*255 if A=B else 0*/
#define AGB 15 /*255 if A>B else 0*/

#define NOP 0 /*Return from CALL*/
#define SSI 1 /*Serial Shift In*/
#define SSO 2 /*Serial Shift Out*/
#define SCL 3 /*Set serial Clock Low*/
#define SCH 4 /*Set serial Clock High*/
#define RET 5 /**/
#define NEW 6 /*Create stack frame*/
#define OLD 7 /*Resume stack frame*/

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
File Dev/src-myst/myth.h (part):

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#define xP 7 /*to PARALLEL output*/

#define xE 8 /*to ENABLE register*/
#define xA 9 /*to O and D (ADD byte to 16-bit register pair)*/
#define xD 10 /*to DATA page register*/
#define xJ 11 /*write JUMP program counter*/
#define xW 12 /*write JUMP WHILE I not zero, decrement I*/
#define xT 13 /*write JUMP if R not zero*/
#define xF 14 /*write JUMP if R zero*/
#define xC 15 /*write CALL page index*/

#define CLR 0 /*Clear (value 0)*/
#define IDO 1 /*Identity O*/
#define OCR 2 /*Ones' complement of R*/
#define OCO 3 /*Ones' complement of O*/
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#define SLO 5 /*Shift left O*/
#define SRR 6 /*Shift right R*/
#define SRO 7 /*Shift right O*/
#define AND 8 /*R AND O*/
#define IOR 9 /*R OR O*/
#define EOR 10 /*R XOR O*/
#define ADD 11 /*R + O*/
#define CAR 12 /*Carry of R + O (0 or 1)*/
#define RLO 13 /*255 if R<O else 0*/
#define REO 14 /*255 if R=O else 0*/
#define RGO 15 /*255 if R>O else 0*/

#define NOP 0 /*No Operation*/
#define SSI 1 /*Serial Shift In*/
#define SSO 2 /*Serial Shift Out*/
#define SCL 3 /*Set serial Clock Low*/
#define SCH 4 /*Set serial Clock High*/
#define RET 5 /*Wide Return*/
#define FAR 6 /*Wide Branch*/
#define SIP 7 /*Get wide PC*/

#define P4 0 /*R PLUS 4*/
#define P1 1
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void
myth_cycle(struct myth_vm *vm) /* Single-step 1 instruction cycle */
{
        vm->scrounge = 0;
        uchar opcode = myth_fetch(vm);

                /*Decode priority encoded opcode*/
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
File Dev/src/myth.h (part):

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#define xP 7 /*to PARALLEL output*/

#define xE 8 /*to ENABLE register*/
#define xA 9 /*to O and D (ADD byte to 16-bit register pair)*/
#define xB 10 /*to DATA page register*/
#define xJ 11 /*write JUMP program counter*/
#define xW 12 /*write JUMP WHILE I not zero, decrement I*/
#define xT 13 /*write JUMP if R not zero*/
#define xF 14 /*write JUMP if R zero*/
#define xC 15 /*write CALL page index*/


/*ALU Instructions
*/

#define CLR 0 /*Clear (value 0)*/
#define IDO 1 /*Identity O*/
#define OCR 2 /*Ones' complement of R*/
#define OCO 3 /*Ones' complement of O*/
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#define SLO 5 /*Shift left O*/
#define SRR 6 /*Shift right R*/
#define SRO 7 /*Shift right O*/
#define AND 8 /*R AND O*/
#define IOR 9 /*R OR O*/
#define EOR 10 /*R XOR O*/
#define ADD 11 /*R + O*/
#define CAR 12 /*Carry of R + O (0 or 1)*/
#define RLO 13 /*255 if R<O else 0*/
#define REO 14 /*255 if R=O else 0*/
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/*SYS Instructions
*/

#define NOP 0 /*No Operation*/
#define SSI 1 /*Serial Shift In*/
#define SSO 2 /*Serial Shift Out*/
#define SCL 3 /*Set serial Clock Low*/
#define SCH 4 /*Set serial Clock High*/
#define RET 5 /*Return to L7:I from nested call*/
#define COR 6 /*Coroutine jump to D:I*/
#define OWN 7 /*Save code page index in L7*/


/*FIX Instructions
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        vm->d = 0;
        vm->l = 0;

        vm->scrounge = 0;
}


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void
myth_step(struct myth_vm *vm)
{
        vm->scrounge = 0;
        uchar opcode = fetch(vm);

        /*Decode priority encoded opcode*/
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
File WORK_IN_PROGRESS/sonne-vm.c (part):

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#include <stdlib.h>
#include <string.h>

#define LHS_N 0 /*Number - Fetch next opcode as literal*/
#define LHS_M 1 /*Memory - Load implicit memory address (xMx)*/
#define LHS_R 2 /*Result - Receives ALU result*/
#define LHS_H 3 /*Hold - Holds high-order return address*/
#define LHS_G 4 /*Global - Global bank register*/
#define LHS_L 5 /*Local - Local bank register*/
#define LHS_S 6 /*Serial - Serial input register*/
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#define RHS_I 0 /*Iteration - Set inner loop counter*/
#define RHS_M 1 /*Memory - Write to implicit memory address (xMx)*/
#define RHS_R 2 /*Result*/
#define RHS_H 3 /*Hold*/
#define RHS_G 4 /*Global*/
#define RHS_L 5 /*Local*/
#define RHS_S 6 /*Serial*/
#define RHS_P 7 /*Parallel*/
#define RHS_E 8 /*Enable - Device enable bits*/
#define RHS_J 9 /*Jump - Unconditional branch*/
#define RHS_D 10 /*Decrement - Branch if iteration register not zero*/
#define RHS_T 11 /*True - Branch if R+O not zero*/
#define RHS_F 12 /*False - Branch if R+0 zero*/
#define RHS_C 13 /*Call - Call subroutine*/
#define RHS_B 14 /*Beta - Accumulator register*/
#define RHS_A 15 /*Alpha - Accumulator register*/
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#define ALU_SLB 5 /*Shift left B*/
#define ALU_SRA 6 /*Shift right A*/
#define ALU_SRB 7 /*Shift right B*/
#define ALU_AND 8 /*A AND B*/
#define ALU_IOR 9 /*A OR B*/
#define ALU_EOR 10 /*A XOR B*/
#define ALU_ADD 11 /*A + B*/
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#define KICK_SCL 3 /*Set serial clock low*/
#define KICK_SCH 4 /*Set serial clock high*/
#define KICK_RDY 5 /*Parallel output state*/
#define KICK_LLF 6 /*Leave local frame*/
#define KICK_ELF 7 /*Enter local frame*/
#define KICK_REA 8 /*Reuse CLIP value in A*/
#define KICK_REB 9 /*Reuse CLIP value in B*/


uint8_t quitf, loggingf;
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    else /*GETPUT*/
    {
        switch(guide) {
        case 1: acc.clip = acc.A; loc = &acc.A; sprintf(msg, "A"); break;
        case 2: acc.clip = acc.B; loc = &acc.B; sprintf(msg, "B"); break;
        case 3: loc = &ALU.R; sprintf(msg, "R"); break;
        }

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             }
             else {
                 mem.data[addr] = *loc;
                 sprintf(msg, "%s PUT %d\n", msg, *loc);
             }
        }
        else // GET
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
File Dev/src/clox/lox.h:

#ifndef __LOX_H__
#define __LOX_H__ 1

/* Definitions and helper functions for LOX vm.
   Sonne 8 micro-controller Rev. Myth/LOX
   Author: mim@ok-schalter.de (Michael/Dosflange@github)
    */

#include <u.h>
#include <libc.h>
#include "myth.h"


/* The following are offsets in 0x7F00 page
 */

#define ARG 0xF7 /*Current argument string offset*/
#define POS 0xF8 /*Output text position offset*/
#define VTP 0xF9 /*VOCAB top page*/
#define VTO 0xFA /*VOCAB top offset*/
#define DESTP 0xFB /*Destination address page*/
#define DESTO 0xFC /*Destination address offs*/
#define SRCP 0xFD /*Source address page*/
#define SRCO 0xFE /*Source address offs*/
#define ECODE 0xFF /*Exit Code*/


/* Application specific opcodes
*/

#define END 0x81 /*0x80 + 16 * Nx + xM // scrounge NM*/


/* Attached virtual devices:
*/

#define SL0_NULL      0    /* NULL device for SL */
#define SL1_PAROE     1    /* CPU parallel port output enable */
#define SL2_SMEMOE    2    /* SMEM data byte output enable */
#define SL3_SMEMWE    3    /* SMEM data byte write enable */

#define SH0_NULL      0    /* NULL device for SH */        
#define SH1_PARLE     1<<4 /* CPU parallel port latch enable */
#define SH2_SMEMA0LE  2<<4 /* SMEM address bit latch 0-7 */
#define SH3_SMEMA1LE  3<<4 /* SMEM address bit latch 8-15 */
#define SH4_SMEMA2LE  4<<4 /* SMEM address bit latch 16-23 */

#endif

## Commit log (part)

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2024-08-12 Check in WIP files
2024-08-12 Fix KiCad files
2024-08-12 Recycle old C assembler and sample asm code
2024-08-12 Track opcode_matrix and debug.txt files for reference
2024-08-13 Add relative JUMPs and add decoders to E register
2024-08-13 Forgot additional files
2024-08-13 Implement state save/load and working single-stepper program
2024-08-13 Add missing calls to close()
2024-08-13 Fix create mode argument
2024-08-13 Add folder structure move files
2024-08-13 Move additional files
2024-08-14 Identify xMx with O
2024-08-14 Identify R register and B accumulator
2024-08-14 Change GETPUT, add Q register
2024-08-14 Add CALLER to SYS group
2024-08-14 Revert Q reg to D
2024-08-14 Add updated schematics plot
2024-08-15 Remove A, try R new/old
2024-08-15 Rework everything
2024-08-16 Remove offset-mapped segmentation
2024-08-16 Fix the schematics
2024-08-16 Add B register
2024-08-16 Add wounded schematics plot
2024-08-16 Fix bug in two adder instances
2024-08-17 Change design using xB(ase) xA(dd) pair
2024-08-17 WIP Edit single-stepper to reflect new KiCad model
2024-08-17 Commit correct/updated PDF
2024-08-17 Change folder structure
2024-08-17 Add small-size jpg
2024-08-18 Clean up the schematics
2024-08-18 Rename folder
2024-08-18 Rename files
2024-08-18 Change file names
2024-08-18 Add schematics
2024-08-18 Move files
2024-08-18 Change folder name
2024-08-18 Rename BRA opcode FAR
2024-08-18 Begin a document
2024-08-18 Check-in correct files
2024-08-18 Add description of serial io instructions
2024-08-21 Rename B register, change functionality of it
2024-08-21 Implement design change re. B register
2024-08-21 Add groff doc source
2024-08-21 Fix spelling mistakes, add paragraph on G,I and xB
2024-08-21 Add PDF version
2024-08-21 Fix wrong doc
2024-08-22 Rename A register to GI
2024-08-22 Rename WTF to JW, JT, JF for clarity
2024-08-22 Update doc
2024-08-24 Add INO/DEO scrounge opcodes
2024-08-24 Add file version signature to vm struct
2024-08-24 refactor doc source
2024-08-25 Change GETPUT opcode encoding
2024-08-25 Check in updated doc pdf
2024-08-25 Update schematics file
2024-08-25 Add strlits.h file for looking up mnemonics to opcodes
2024-08-26 Switch back to absolute addressing
2024-08-26 Refactor myst files, write skeletons for nettle/lox assembly
2024-08-26 Fix nettle bugs to find .h files
2024-08-26 Fix nettle to runnable
2024-08-28 Add legacy files state for creating lox.asm
2024-08-29 Remove stuff and add Nettle assembler
2024-08-29 Add LOX repl
2024-08-30 Write register dump utility
2024-08-30 Add locals display
2024-08-30 Fix reset PC if exitcode
2024-08-30 Add little tools and shell scripts
2024-08-30 Fix missing break; bug in GETPUT switch statement
2024-08-30 Add native multiplication routine
2024-08-31 Fix renaming j to pc in .h users
2024-08-31 Fix names re. J, adjust opcodes and fix scrounger section in schematics
2024-08-31 Add native division routine
2024-09-01 Implement changed semantics of xA in KiCad and myth[...].h
2024-09-01 Write native dictionary look-up routine
2024-09-01 Increase cycle count in lox.c and clarify output
2024-09-01 Replace ALU opcode IDR with CLR (set R to zero)
2024-09-02 Shorten ADJUST to FIX, rename FIX type opcodes
2024-09-02 Add native VSrch and PrMsg functions. Implement application-specific opcode END
2024-09-03 Implement native CLI and relocate object code
2024-09-03 Add test for valid CMD and code to execute it
2024-09-03 Create assembler stubs and symtab entries for upcoming commands
2024-09-03 Add additional stubs and symbols
2024-09-04 Fix bug in lox.c clobbering image system vars in the init part
2024-09-04 Initial WIP exchanging DO register pair for GI register pair during CALL/RET
2024-09-04 Finish changes in KiCad file
2024-09-04 Add changes regarding DO->GI that don't require instruction set changes
2024-09-04 Change Ix to Dx globally
2024-09-04 Finish hardware changes
2024-09-04 Change all function prologs/epilogs from DO to GI
2024-09-04 Work on regression bugs due to design changes
2024-09-04 Fix naming of roid vs. giro
2024-09-04 Swap xI with xD in pair decoder, KiCad only
2024-09-04 Fix clobbered hex code literals after global replace error
2024-09-05 Simplify the design for nicer programming: Remove G register, re-introduce ENTER and LEAVE, add relative addressing
2024-09-05 Clear out legacy symbol table (generated at runtime now)
2024-09-05 Fix KiCad schematics and POC native code
2024-09-05 Rename G to D as before (D for Data)
2024-09-05 Add untracked files
2024-09-06 Refactor myth.h
2024-09-06 Relocate pre-built symbol table
2024-09-06 Fix native assembler source
2024-09-06 Remove outdated documentation
2024-09-06 Write native SkipNULL function (advance to next NULL byte)
2024-09-06 Refactor VSrch
2024-09-07 Fix double paren
2024-09-07 Fix: Reset POS when terminating a Lox run
2024-09-07 Change mnemonic for NEW to OWN and reorder VM struct
2024-09-07 Clean up myth.h
2024-09-07 Change NEW to OWN in nettle.c
2024-09-07 Add code to generate JSON opcode table
2024-09-07 Create JSON file with info on each instruction
2024-09-07 Move JSON file to src
2024-09-07 Add pc incrementation explicitly
2024-09-07 Revise opcodes JSON
2024-09-07 Add version info
2024-09-08 Add hardware interrupt system
2024-09-08 Add things to JSON file
2024-09-08 Add interrupt system to myth.h
2024-09-08 Add HTML generation
2024-09-08 Fix bugs and add to html generator code
2024-09-08 Add skeleton generator for automated HTML documentation
2024-09-09 Add work on automatically generating HTML docs
2024-09-09 Committing the correct file
2024-09-09 Add more documentation code
2024-09-10 Add final version with HTML generation code
2024-09-10 Remove HTML stuff
2024-09-10 Add auto-generated HTML doc
2024-09-10 Add missing doc file stubs
2024-09-10 Escape special chars in HTML code for ALU instructions
2024-09-10 Changes to HTML documents, add content on device IO
2024-09-10 Update index.html with doc progress
2024-09-11 Fix incorrect letter prefix
2024-09-11 Fix/add docs for scrounge opcodes
2024-09-11 Fix double 'encoding' line in SYS opcode pages
2024-09-11 Add doc. about notation
2024-09-11 Add tentative lox export as text file for scrap
2024-09-11 Remove src export code
2024-09-11 Remove css file
2024-09-13 Add initial version of Goldie assembler
2024-09-13 Fix error in encoding line
2024-09-13 Add predefined symbols asm file
2024-09-13 Add current state of new assembler
2024-09-13 Add slightly revised schematics
2024-09-13 Add assembler listing
2024-09-14 Fix bug in comment handler
2024-09-14 Fix lid overflow bug, add symbol table source to asm file
2024-09-14 Fix bug in listing generator
2024-09-14 Add json description file
2024-09-14 Improve formatting, comment assembler file
2024-09-14 For git
2024-09-14 Reformat and check imported asm from previous assembler (Nettle)
2024-09-14 Finish reformatting asm file
2024-09-14 Fix avoid string-context in comments and vice versa
2024-09-15 Add html documentation and images
2024-09-15 Add missing closing tag
2024-09-15 Clarify text
2024-09-15 Fix image, add schematics update
2024-09-15 Make various pending updates
2024-09-15 Fix bug in handling of string literals
2024-09-15 Fix bug in handling of parens in string runs
2024-09-15 Add README file with dev instructions
2024-09-15 Update build scripts
2024-09-16 Fix bugs in firmware code
2024-09-16 Clarify a comment
2024-09-16 Reformat source file
2024-09-16 Add comments
2024-09-16 Add example of defined constants
2024-09-16 Simplify dev folder
2024-09-16 Add stub and cli arguments for loadfile()
2024-09-16 Add defines for virtual device 'SMEM'
2024-09-16 Split e register state into e_old and e_new to allow for signal edge detection
2024-09-17 Change virtual IO handler section
2024-09-17 Why?
2024-09-17 Add virtual smem device and signal handling
2024-09-17 Add provision for ramdisk file
2024-09-17 Create LOX device constants in firmware source
2024-09-17 Mention a bug
2024-09-21 Fix bug in schematics
2024-09-21 Pending commit for pull
2024-09-26 Fix bugs in schematics
2024-09-26 Break monolithic schematics into six boards with shared pin-headers
2024-09-26 Reduce number of shared headers
2024-09-27 Improve schematics for readability
2024-09-27 Port SPI RD/WR functions tested on prototype
2024-10-11 For rebasing
2024-10-11 Change d to g
2024-10-11 Write generator program and vtable emulator stub
2024-10-11 Fix bugs in vtable.c
2024-10-11 Change d to g in docs
2024-10-11 Global change l to g
2024-10-11 Check in missing file
2024-10-11 Fix Nx instructions reg. PC++
2024-10-11 Change E register semantics
2024-10-12 Change CO do D
2024-10-13 Clean up reference implementation
2024-10-13 Add documentation
2024-10-13 Add comments in ref. implementation
2024-10-14 Change COR to use R
2024-10-17 Fix documentation re: change d->g
2024-10-17 More doc fixes
2024-10-18 Fix TRAP vs. PAIR
2024-10-18 Fix pair.html refs to d
2024-10-18 Update pencoder image
2024-10-18 Fix doc
2024-10-18 Change website landing
2024-10-18 Fix section on pointers
2024-10-18 Fix spelling
2024-10-18 Fix broken a tag
2024-10-18 Change semantics of xB
2024-10-18 Change signal names
2024-10-18 Let defines/labels diverge from assembler mnemonics
2025-01-13 Uses KiCAD buses, remove COR and OWN instructions and xB
    Change memory logic to save code page on calls. Software tools don't reflect this version yet.
2025-05-29 Upload hw bug fix
2025-06-12 Update README.md Update link to documentation website
